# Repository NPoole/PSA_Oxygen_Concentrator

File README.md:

# PSA_Oxygen_Concentrator
An Oxikit-style Pressure Swing Adsorption Oxygen concentrator

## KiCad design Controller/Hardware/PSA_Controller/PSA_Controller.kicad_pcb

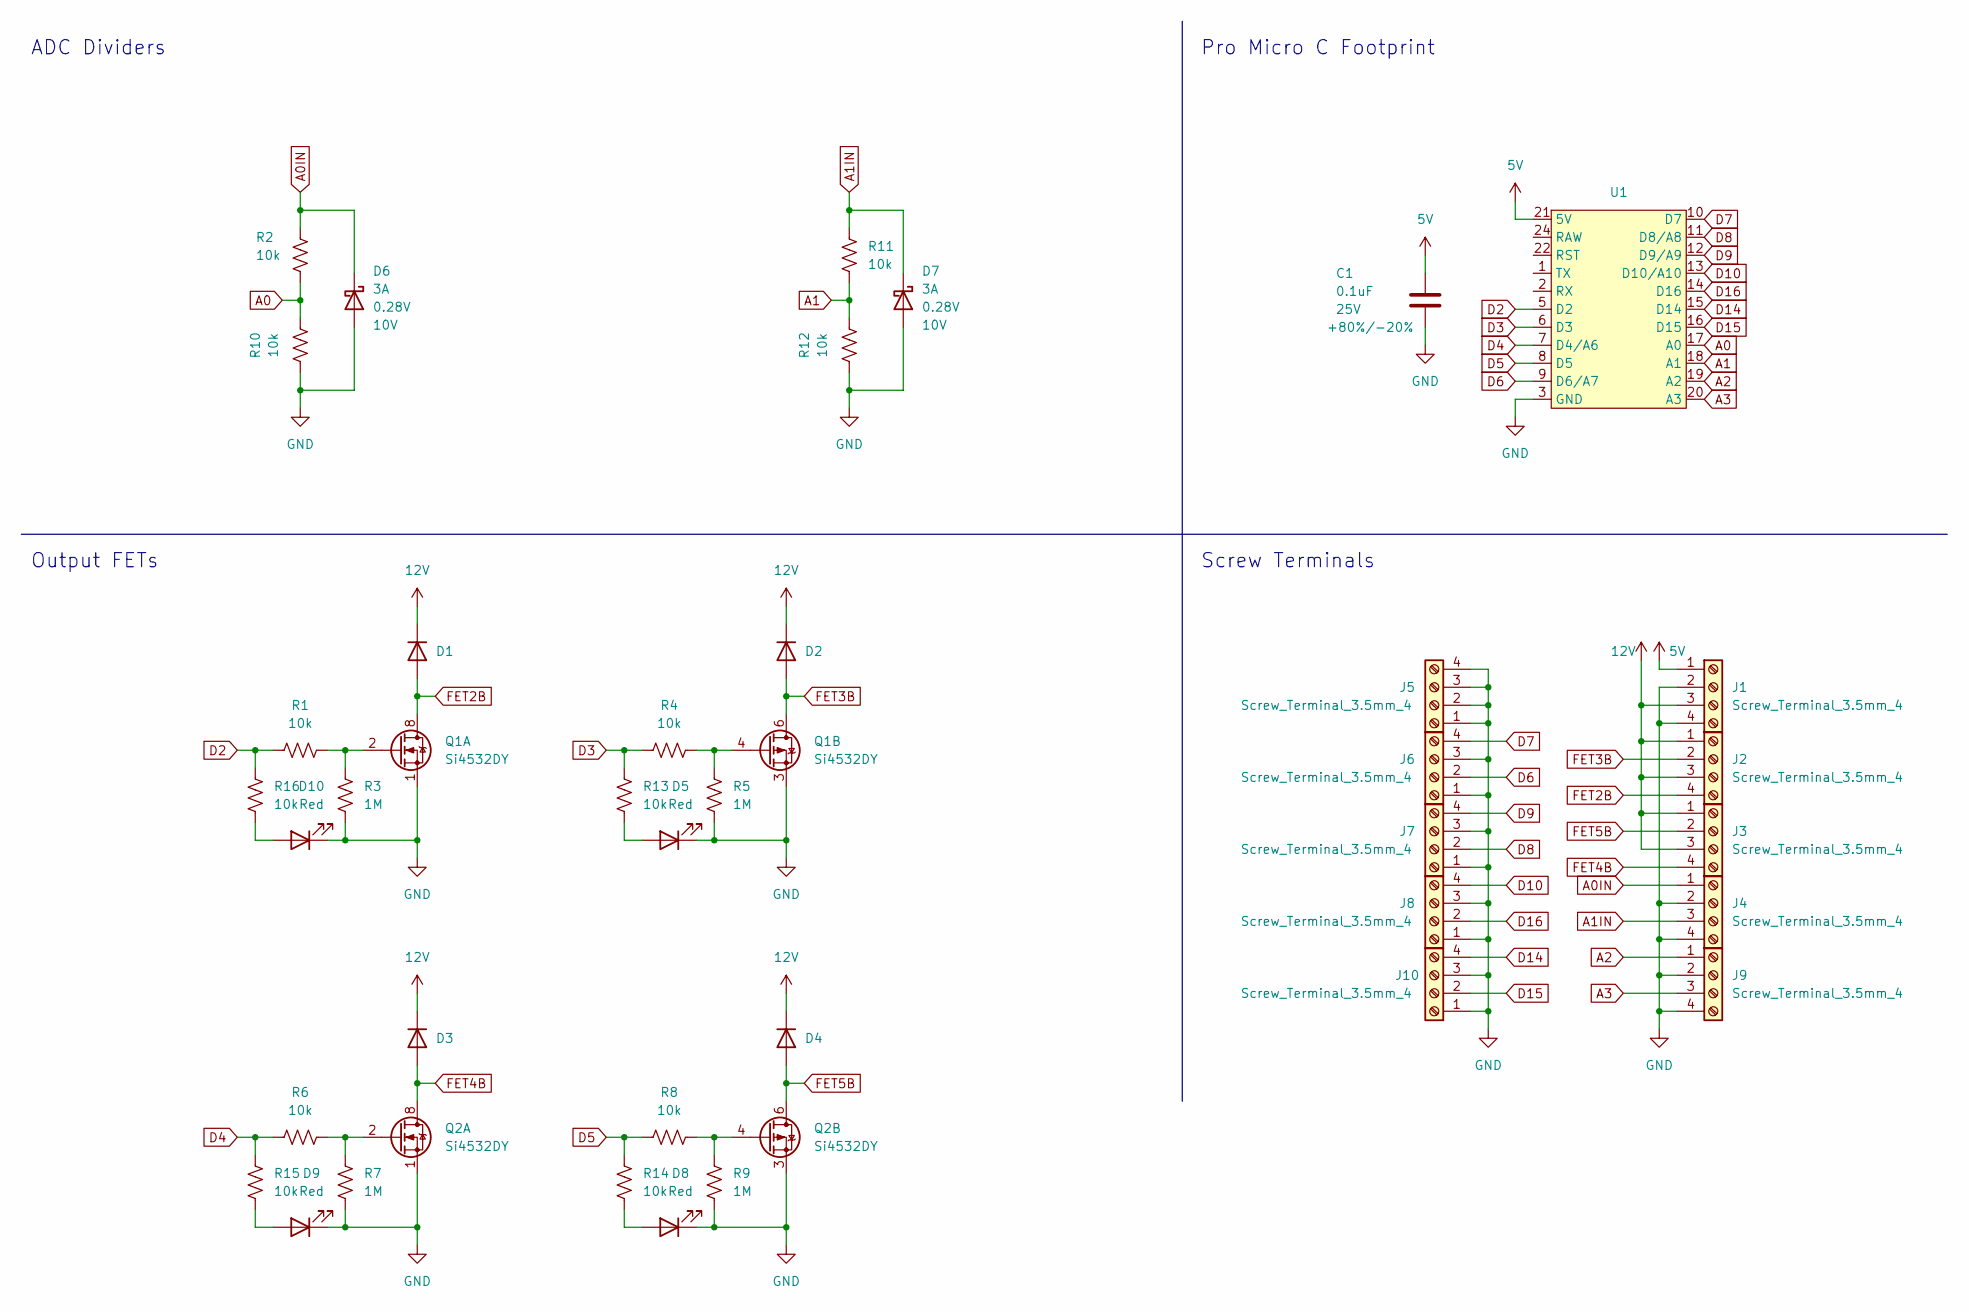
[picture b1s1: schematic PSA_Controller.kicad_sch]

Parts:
C1: 0.1uF; C_0603_1608Metric; Voltage 25V; Tolerance +80%/-20%
D1, D2, D3, D4: SOD-323
D5, D8, D9, D10: Red; LED_0603_1608Metric
D6, D7: 3A; SOD-323
J1, J2, J3, J4, J5, J6, J7, J8, J9, J10: Screw_Terminal_3.5mm_4; SCREWTERMINAL-3.5MM-4
Q1, Q2: Si4532DY; SOIC-8_3.9x4.9mm_P1.27mm
R1, R2, R4, R6, R8, R10, R11, R12, R13, R14, R15, R16: 10k; R_0603_1608Metric
R3, R5, R7, R9: 1M; R_0603_1608Metric
U1: P

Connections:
5V: C1.1, J1.1, U1.21 (5V)
12V: D1.C, D2.C, D3.C, D4.C, J1.3, J2.1, J2.3, J3.1, J3.3
A0: R2.2, R10.2, U1.17 (A0)
A0IN: D6.C, J4.1, R2.1
A1: R11.1, R12.2, U1.18 (A1)
A1IN: D7.C, J4.3, R11.2
A2: J9.1, U1.19 (A2)
A3: J9.3, U1.20 (A3)
D2: R1.1, R16.2, U1.5 (D2)
D3: R4.1, R13.2, U1.6 (D3)
D4: R6.1, R15.2, U1.7 (D4/A6)
D5: R8.1, R14.2, U1.8 (D5)
D6: J6.2, U1.9 (D6/A7)
D7: J6.4, U1.10 (D7)
D8: J7.2, U1.11 (D8/A8)
D9: J7.4, U1.12 (D9/A9)
D10: J8.4, U1.13 (D10/A10)
D14: J10.4, U1.15 (D14)
D15: J10.2, U1.16 (D15)
D16: J8.2, U1.14 (D16)
FET2B: D1.A, J2.4, Q1.7 (D), Q1.8 (D)
FET3B: D2.A, J2.2, Q1.5 (D), Q1.6 (D)
FET4B: D3.A, J3.4, Q2.7 (D), Q2.8 (D)
FET5B: D4.A, J3.2, Q2.5 (D), Q2.6 (D)
GND: C1.2, D5.1 (K), D6.A, D7.A, D8.1 (K), D9.1 (K), D10.1 (K), J1.2, J1.4, J4.2, J4.4, J5.1, J5.2, J5.3, J5.4, J6.1, J6.3, J7.1, J7.3, J8.1, J8.3, J9.2, J9.4, J10.1, J10.3, Q1.1 (S), Q1.3 (1), Q2.1 (S), Q2.3 (1), R3.2, R5.2, R7.2, R9.2, R10.1, R12.1, U1.3 (GND), U1.4 (GND), U1.23 (GND)
unnamed: D5.2 (A), R13.1
unnamed: D8.2 (A), R14.1
unnamed: D9.2 (A), R15.1
unnamed: D10.2 (A), R16.1
unnamed: Q1.2 (G), R1.2, R3.1
unnamed: Q1.4 (G), R4.2, R5.1
unnamed: Q2.2 (G), R6.2, R7.1
unnamed: Q2.4 (G), R8.2, R9.1

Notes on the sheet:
Pro Micro C Footprint
ADC Dividers
Screw Terminals
Output FETs

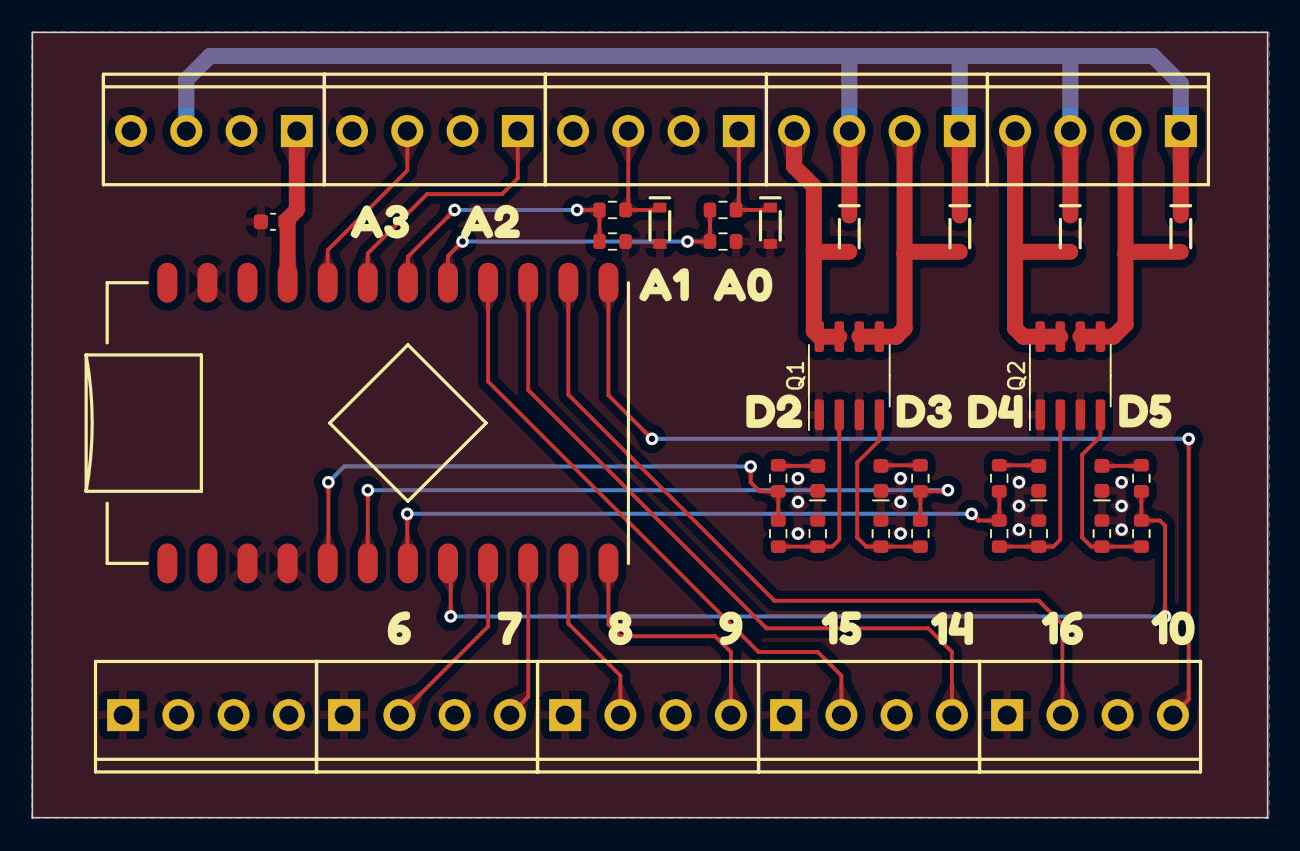
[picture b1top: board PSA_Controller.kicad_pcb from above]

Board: 2 copper layers, 78.2 x 49.8 mm, 56 parts (0 on the bottom side), 33 nets.

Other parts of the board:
kibuzzard-65A2DED7: G***; kibuzzard-65A2DED7
kibuzzard-65A2DEE2: G***; kibuzzard-65A2DEE2
kibuzzard-65A2DF0B: G***; kibuzzard-65A2DF0B
kibuzzard-65A2DF03: G***; kibuzzard-65A2DF03
kibuzzard-65A2DF4A: G***; kibuzzard-65A2DF4A
kibuzzard-65A2DF5D: G***; kibuzzard-65A2DF5D
kibuzzard-65A2DF6F: G***; kibuzzard-65A2DF6F
kibuzzard-65A2DF9C: G***; kibuzzard-65A2DF9C
kibuzzard-65A2DF36: G***; kibuzzard-65A2DF36
kibuzzard-65A2DFAB: G***; kibuzzard-65A2DFAB
kibuzzard-65A2DFB3: G***; kibuzzard-65A2DFB3
kibuzzard-65A2DFBB: G***; kibuzzard-65A2DFBB
kibuzzard-65A2DFC2: G***; kibuzzard-65A2DFC2
kibuzzard-65A2DFD0: G***; kibuzzard-65A2DFD0
kibuzzard-65A2DFDA: G***; kibuzzard-65A2DFDA
kibuzzard-65A2DFE3: G***; kibuzzard-65A2DFE3

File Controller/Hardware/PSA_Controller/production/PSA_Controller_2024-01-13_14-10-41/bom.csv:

Designator,Footprint,Quantity,Value,LCSC Part #
C1,0603,1,0.1uF,
"D1, D2, D3, D4",SOD-323,4,~,
"D10, D5, D8, D9",0603,4,Red,
"D6, D7",SOD-323,2,3A,
"J1, J10, J2, J3, J4, J5, J6, J7, J8, J9",SCREWTERMINAL-3.5MM-4,10,Screw_Terminal_3.5mm_4,
"Q1, Q2",SOIC-8_3.9x4.9mm_P1.27mm,2,Si4532DY,
"R1, R10, R11, R12, R13, R14, R15, R16, R2, R4, R6, R8",0603,12,10k,
"R3, R5, R7, R9",0603,4,1M,
U1,P,1,~,

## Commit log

2024-06-01 Initial Upload
